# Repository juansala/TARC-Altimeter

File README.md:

# TARC-Altimeter

PCB and firmware for custom altimeter based off AtTiny85 and BMP280 pressure sensor, as well as COTS altimeters. For use in low to high power rocketry.

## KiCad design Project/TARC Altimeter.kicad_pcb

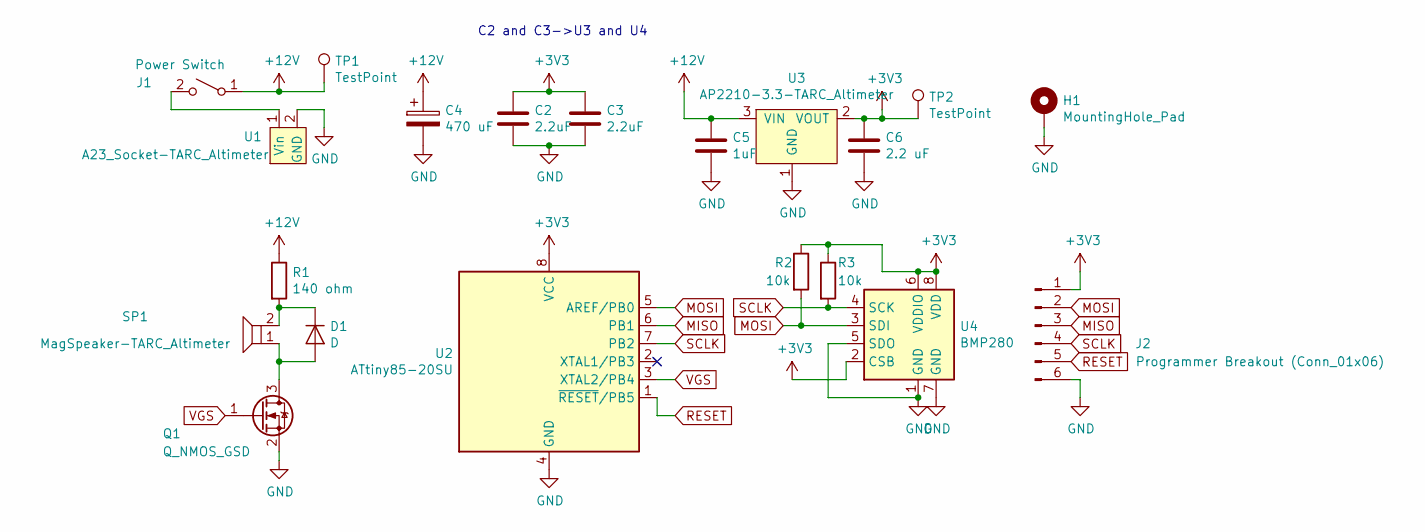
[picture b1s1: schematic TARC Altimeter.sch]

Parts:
C2, C3: 2.2uF; C_0805_2012Metric_Pad1.15x1.40mm_HandSolder
C4: 470 uF; C_Radial_D8.0mm_H7.0mm_P3.50mm
C5: 1uF; C_0805_2012Metric_Pad1.15x1.40mm_HandSolder
C6: 2.2 uF; C_0805_2012Metric_Pad1.15x1.40mm_HandSolder
D1: D; D_0805_2012Metric_Pad1.15x1.40mm_HandSolder
H1: MountingHole_Pad; MountingHole_3.2mm_M3_DIN965_Pad
J1: Power Switch; PinHeader_1x02_P1.27mm_Vertical
J2: Programmer Breakout (Conn_01x06); PinHeader_2x03_P2.54mm_Vertical
Q1: Q_NMOS_GSD; SOT-23
R1: 140 ohm; R_0805_2012Metric_Pad1.15x1.40mm_HandSolder
R2, R3: 10k; R_0805_2012Metric_Pad1.15x1.40mm_HandSolder
SP1: MagSpeaker-TARC_Altimeter; WT-1205
TP1, TP2: TestPoint; TestPoint_Pad_D1.5mm
U1: A23_Socket-TARC_Altimeter; A23_Socket
U2: ATtiny85-20SU; SOIJ-8_5.3x5.3mm_P1.27mm
U3: AP2210-3.3-TARC_Altimeter; SOT-23
U4: BMP280; Bosch_LGA-8_2x2.5mm_P0.65mm_ClockwisePinNumbering

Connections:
+3V3: C2.1, C3.1, C6.1, J2.1, R2.1, R3.1, TP2.1, U2.8 (VCC), U3.2 (VOUT), U4.2 (CSB), U4.6 (VDDIO), U4.8 (VDD)
+12V: C4.1, C5.1, J1.1 (A), R1.1, TP1.1, U3.3 (VIN)
GND: C2.2, C3.2, C4.2, C5.2, C6.2, H1.1, J2.6, Q1.2 (S), U1.2 (GND), U2.4 (GND), U3.1 (GND), U4.1 (GND), U4.5 (SDO), U4.7 (GND)
MISO: J2.3, U2.6 (PB1)
MOSI: J2.2, R2.2, U2.5 (AREF/PB0), U4.3 (SDI)
unnamed: D1.1 (K), R1.2, SP1.2
unnamed: D1.2 (A), Q1.3 (D), SP1.1
unnamed: J1.2 (B), U1.1 (Vin)
RESET: J2.5, U2.1 (~RESET~/PB5)
SCLK: J2.4, R3.2, U2.7 (PB2), U4.4 (SCK)
VGS: Q1.1 (G), U2.3 (XTAL2/PB4)

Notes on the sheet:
C2 and C3->U3 and U4

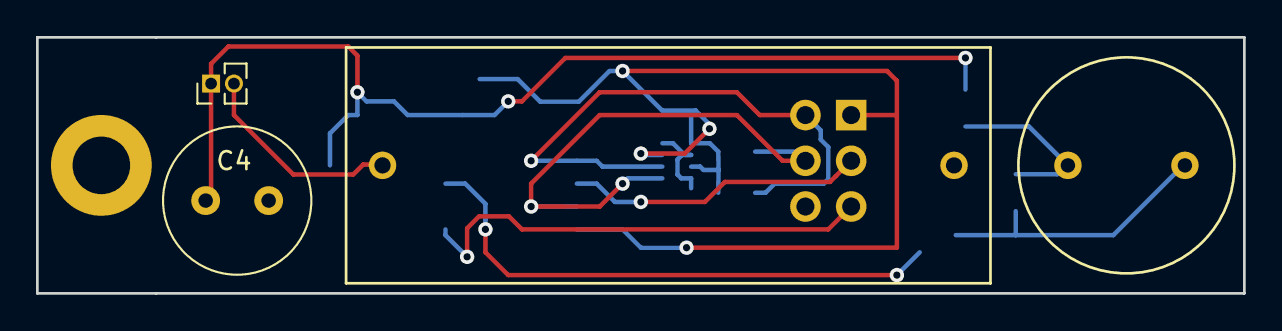
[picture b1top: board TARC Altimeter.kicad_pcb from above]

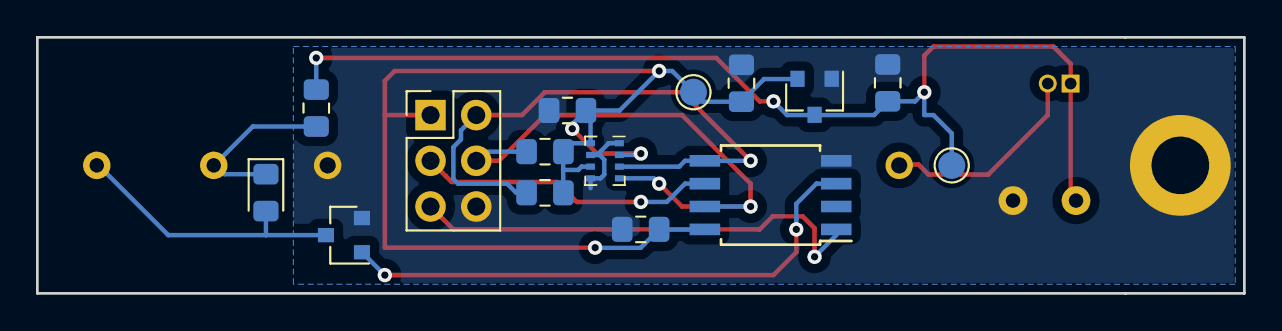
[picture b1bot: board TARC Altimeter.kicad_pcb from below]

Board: 2 copper layers, 67.1 x 14.2 mm, 20 parts (15 on the bottom side), 11 nets.

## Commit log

2020-09-03 actually added test KiCAD archive ZIP
2020-09-03 saved KiCAD project
2020-11-27 added BOM
2020-12-05 added altimeter script
2020-12-07 added example BMP280 code
2020-12-30 added i2c pullups and rearranged components, finalized BMP280 test script
2020-12-31 changed VGS pin
